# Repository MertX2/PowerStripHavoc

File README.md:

# PowerStripHavoc
PowerStripHavoc is a WIP power regulation PCB for Wii Portables that sits on top of the Wii mainboard and inbetween the CPU and GPU. It is heavily inspired by YveltalGriffin's [Thundervolt](https://github.com/mackieks/thundervolt) , loopj's [short stack](https://github.com/loopj/short-stack) project and different PCBs, and the [RVL-PMS](https://github.com/Gmanmodz/RVL-Power-Management-System) by gmanmodz. 

Its name is a combination of loopj's PowerStrip, which is the base of this project, and the Havoc weapon from Apex Legends. 

This Project is currently in the testing phases and is in no way ready to be used.

# Firmware
The firmware is written in Cpp using the Arduino Framework via [megaTinyCore](https://github.com/SpenceKonde/megaTinyCore) .
In order to compile it, you just need VSCode with the PlatformIO addon installed.

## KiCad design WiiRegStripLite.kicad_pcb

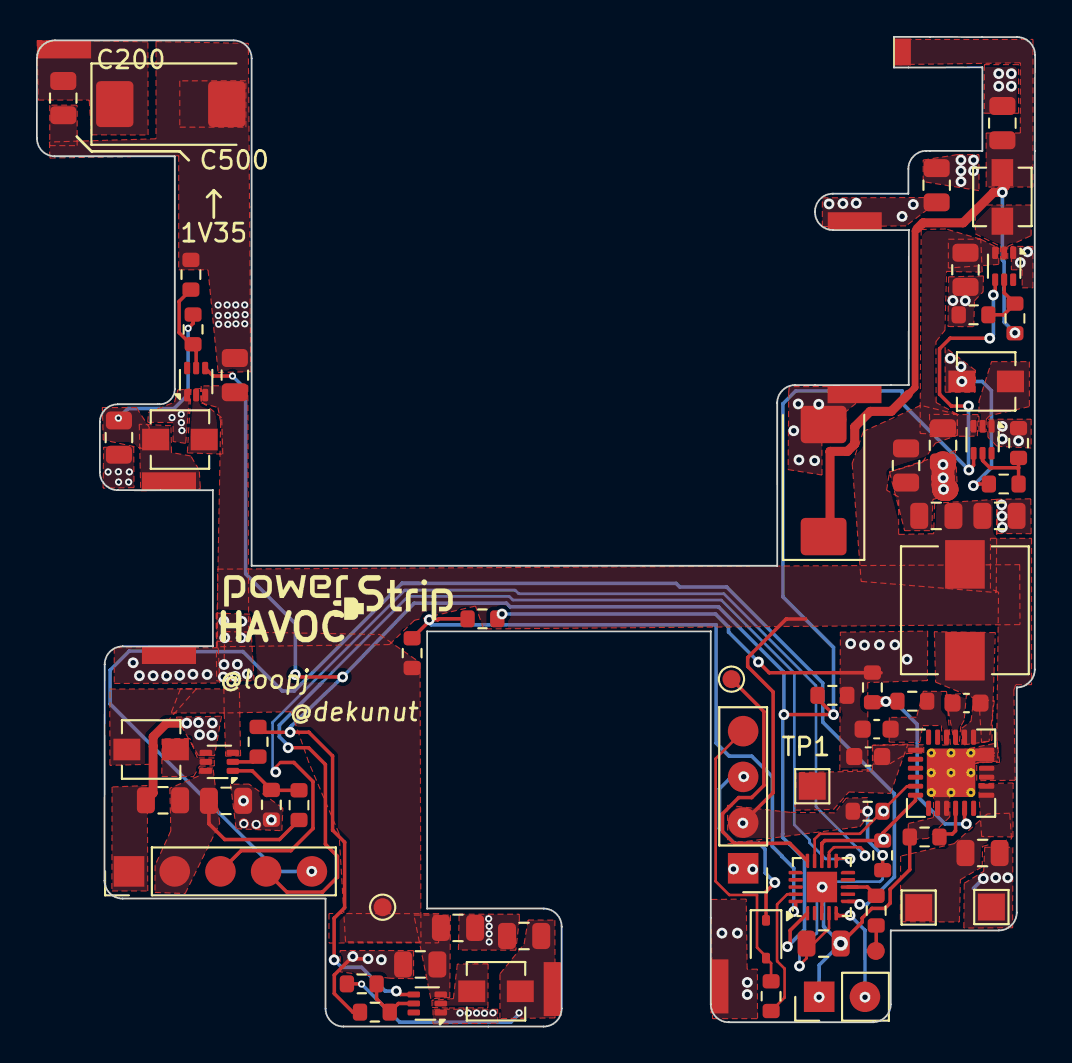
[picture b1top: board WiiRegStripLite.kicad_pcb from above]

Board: 2 copper layers, 55.5 x 55.0 mm, 72 parts (0 on the bottom side), 39 nets.

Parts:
C1: 1uf; C_0603_1608Metric
C7: 0.047uf; C_0603_1608Metric
C11: 4.7uf; C_0603_1608Metric
C12, C13, C14, C14#2, C15, C26: 10uf; C_0805_2012Metric
C16, C17, C18, C19: 10uF; C_0805_2012Metric
C20, C21, C22, C23, C24, C25: 22uF; C_0805_2012Metric
C189: 220uF; CP_EIA-7343-20_Kemet-V
C200: 11uF; C_0805_2012Metric
C500: 150uF; CP_EIA-7343-20_Kemet-V
D1: B5819W; D_SOD-323
GND: BAT+; TestPoint_Pad_1.5x1.5mm
J1: Conn_01x04_Socket; PinHeader_1x04_P2.54mm_Vertical
J2: Conn_01x04_Socket; PinHeader_1x05_P2.54mm_Vertical
J3: Fan; PinHeader_1x02_P2.54mm_Vertical
L5: 2.2uh; L_Wuerth_HCI-7030
L6, L7, L8, L9, L10: 1uH; L_Vishay_IHLP-1212
R1: 261; R_0603_1608Metric
R10, R11, R12, R13, R27, R28: 10k; R_0603_1608Metric
R14: 66.5K; R_0603_1608Metric
R15, R17, R19, R21: 100K; R_0603_1608Metric
R16: 80k; R_0603_1608Metric
R18: 414k; R_0603_1608Metric
R20: 470; R_0603_1608Metric
R22: 124k; R_0603_1608Metric
R23: 100; R_0603_1608Metric
R24: 732k; R_0603_1608Metric
R25, R26: 100k; R_0603_1608Metric
TH1: 10k; R_0603_1608Metric
TP1: CHRG; TestPoint_Pad_1.5x1.5mm
TP2: BAT+; TestPoint_Pad_1.5x1.5mm
TP3, TP60: TestPoint; TestPoint_Pad_D1.0mm
TP4: U10; TestPoint_Pad_D1.0mm
TP5, TP7: GND; TestPoint_Pad_3x1.0mm
TP10: 3V3; TestPoint_Pad_1.5x1.0mm
TP20: 1V8; TestPoint_Pad_3x1.0mm
TP30: 1V15; TestPoint_Pad_3x1.0mm
TP40: 1V0; TestPoint_Pad_3x1.0mm
U5: BQ25895RTW; BQ25895
U6: ATtiny1616-M; VQFN-20-1EP_3x3mm_P0.4mm_EP1.7x1.7mm
U7, U8, U9, U10: TLV62585DRL; SOT-563
U11: TPS61023DRLR; SOT-563

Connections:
1V: C20.1, L6.2, R14.1, TP40.1
1V08: C21.1, L7.2, R16.1, TP30.1
1V35: C22.1, C200.1, C500.1, L8.2, R22.1, TP20.1
3V: C23.1, C189.1, L9.2, R18.1, TP10.1
5V: C24.1, C25.1, J2.2, R24.1, U11.6 (VOUT)
/Inductor3vIn: L9.1, U10.2 (SW)
/L1v: L6.1, U7.2 (SW)
/L1v08: L7.1, U8.2 (SW)
/L1v35: L8.1, U9.2 (SW)
/L5v: L10.1, U11.5 (SW)
/LBQ: C7.2, L5.2, U5.19 (SW), U5.20 (SW)
BTN: J2.5, U6.6 (PA5)
EN: R26.2, R28.2, U6.1 (PA2), U7.4 (EN), U8.4 (EN), U9.4 (EN), U10.4 (EN)
GND: C1.1, C11.2, C12.2, C13.1, C14.1, C14#2.1, C15.1, C16.2, C17.2, C18.2, C19.2, C20.2, C21.2, C22.2, C23.2, C24.2, C25.2, C26.1, C189.2, C200.2, C500.2, GND.1, J1.1, J2.1, J3.1, R1.1, R11.1, R15.2, R17.2, R19.2, R21.2, R25.2, R28.1, TH1.2, TP5.1, TP7.1, U5.8 (OTG), U5.9 (~CE), U5.17 (PGND), U5.18 (PGND), U5.25 (PGND), U6.3 (GND), U6.21 (GND), U7.1 (GND), U8.1 (GND), U9.1 (GND), U10.1 (GND), U11.4 (GND)
NeoPixelDIN: R23.1, TP60.1
unnamed: C12.1, TP2.1, U5.13 (BAT), U5.14 (BAT)
unnamed: D1.2 (A), J1.4, R20.1
unnamed: D1.1 (K), J1.3
unnamed: C7.1, U5.21 (BTST)
unnamed: R1.2, U5.10 (ILIM)
unnamed: C11.1, R10.2, U5.22 (REGN)
unnamed: R10.1, R11.2, U5.11 (TS)
unnamed: C1.2, TP1.1, U5.1 (VBUS)
unnamed: R14.2, R15.1, U7.5 (FB)
unnamed: R16.2, R17.1, U8.5 (FB)
unnamed: R19.1, R22.2, U9.5 (FB)
unnamed: R18.2, R21.1, U10.5 (FB)
unnamed: R26.1, U11.2 (EN)
unnamed: R24.2, R25.1, U11.1 (FB)
PA1: R27.1, TH1.1, U6.20 (PA1)
PA4: J3.2, U6.5 (PA4)
PA7: R23.2, U6.8 (PA7)
PC0: TP4.1, U6.15 (PC0)
RX: J2.4, U6.11 (PB3)
SCL: R13.2, U5.5 (SCL), U6.14 (PB0)
SDA: R12.1, U5.6 (SDA), U6.13 (PB1)
TX: J2.3, U6.12 (PB2)
UPDI: R20.2, U6.19 (~RESET/PA0)
VIN: C13.2, C14.2, C14#2.2, C15.2, C16.1, C17.1, C18.1, C19.1, C26.2, J1.2, L5.1, L10.2, R12.2, R13.1, R27.2, TP3.1, U5.15 (SYS), U5.16 (SYS), U6.4 (VCC), U7.3 (VIN), U8.3 (VIN), U9.3 (VIN), U10.3 (VIN), U11.3 (VIN)

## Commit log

2024-09-08 Integrated Power Strip, working on regulators and bq
2024-09-08 More Reg Work, MCU placement
2024-09-09 More work
2024-09-13 Final Design
2024-09-13 Gerber gen and new ibom
2024-09-14 More edits
    Rounded edges, moved traces, added EN pull down resistor
2024-09-22 Some work
2024-09-25 Reg Setup BQ
2024-09-27 Registers Configured
2024-09-28 Started work on config functions
2024-09-28 Added Gitignore to not clutter the backup folder
2024-09-28 A LOT of firmware work
2024-09-29 Firmware optimization
    Implemented sleep states, energy saving, adc register control, adc freerun mode, adc accumulation, interrupt service routines for waking from deep sleep,
    fancheck, powerbuttoncheck, working on batVoltage percentage calculator
2024-09-30 Final touches
    Implemented NeoPixelTask, implemented Battery levels, implemented different RegValueCalculations
2024-10-01 Some more work
2024-10-03 Added U10 emulation on TX Pad of pcb
2024-10-03 Cleanup
2024-10-04 EN pin testing
2024-10-04 Firmware Testing
2024-10-05 More firmware Testing
2024-10-13 Rewrote Code to conform to MSB convention of the BQ chip
2024-10-17 Testing function
2024-10-25 Changed REG init code
2024-10-27 Fixed Master setting and added pin and clock defines
2024-10-28 I2C Comms are working, now have to iron out the bugs.
2024-11-02 Clean up and fixed the reg writes
2024-11-03 testing
